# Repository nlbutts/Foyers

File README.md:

# Foyers / BackPorch Project

The Foyers/BackPorch system is an STM32-based hardware ecosystem designed for FRC robot sensing and control, featuring CAN communication with a built-in bootloader.

## Hardware Overview

### Foyer Distribution Board
The Foyer board serves as the primary distribution point for the system. 
- **Power & CAN Input**: Connects to the main robot power and CAN bus.
- **Power & CAN Exit**: Provides a pass-through for daisy-chaining CAN and power to subsequent devices.
- **Node Interface**: Distributes power and CAN to the BackPorch and sensor nodes.

### BackPorch Main Board
The BackPorch is the central controller board, based on the STM32G0B1 microcontroller. It handles high-level CAN communication, sensor aggregation, and basic power management.

#### Main Connectors & Pinouts

| Ref | Type | Function | Mating Part |
| --- | --- | --- | --- |
| **J4** | RJ45 | CAN Bus | Standard RJ45 Plug |
| **J9** | JST PH 6-pin | Rev Through Bore Encoder | JST PHR-6 |
| **J10** | USB Micro B | Power / Debug | Standard Micro-USB |
| **J1/J2**| Wago 2601 | Power Input (VBAT/GND) | 24-16 AWG Wire |
| **J3** | Wago 2601 | Motor Output | 24-16 AWG Wire |
| **J6** | Tag-Connect | SWD Programming | TC2030-IDC |

**J4 (RJ45) CAN Pinout:**
- **Pin 1**: CAN High
- **Pin 2**: CAN Low
- **Pin 3**: CAN High Loopback
- **Pin 4**: VBAT
- **Pin 5**: VBAT
- **Pin 6**: Can Low Loopback
- **Pin 7**: GND
- **Pin 8**: GND

**J9 (Rev Through Bore Encoder) Pinout:**
Compatible with the [REV Through Bore Encoder](https://docs.revrobotics.com/rev-crossover-products/sensors/tbe).
- **Pin 1**: 5V Power
- **Pin 2**: Absolute Position (Duty Cycle)
- **Pin 3**: Incremental Channel A
- **Pin 4**: Incremental Channel B
- **Pin 5**: Index (Optional)
- **Pin 6**: GND

### SimpleTOF Board
A compact Time-of-Flight (ToF) distance sensor breakout designed to interface with the BackPorch.

## Software Setup

### Development Environment
This project uses the official STM32 development workflow:

1.  **STM32CubeMX**: Used for low-level hardware configuration (GPIO, CAN, Timers).
    - Open the `.ioc` files in the `software/backporch` or `software/bootloader` directories to modify the hardware configuration.
    - Generate code to update the underlying HAL drivers.
2.  **Visual Studio Code**: The recommended IDE for code development.
    - Use the **STM32 VS Code Extension** to compile the project.
    - Ensure `arm-none-eabi-gcc` is installed and in your PATH.
    - Build using the `CMake` workflow provided by the extension.

## Bootloader & Monitoring Utility

The `software/can_mon/bp_debug.py` program is a multi-purpose Python utility for interacting with the hardware over CAN.

### Script Purpose
- **CAN Monitor**: Provides a real-time GUI to view telemetry from discovered devices (Voltage, Current, Temp, Distance, Encoder position).
- **Firmware Updater**: Acts as the host tool for the CAN bootloader, allowing you to stream `.bin` files to a target device ID and commit them to flash.
- **Status Broadcasts**: Decodes the WPILib-formatted CAN frames used by the system.

### Usage
```bash
python software/can_mon/bp_debug.py
```
*Note: Requires `python-can` and `tkinter` libraries. Ensure your CAN adapter is configured (default: SLSAN on COM5).*

## System Architecture

The system follows a modular architecture where multiple sensor nodes (Foyers) communicate with the BackPorch controller over a shared CAN bus, which then interfaces with the Robot Controller.

These are similar to the SWYFT CAN wiring devices

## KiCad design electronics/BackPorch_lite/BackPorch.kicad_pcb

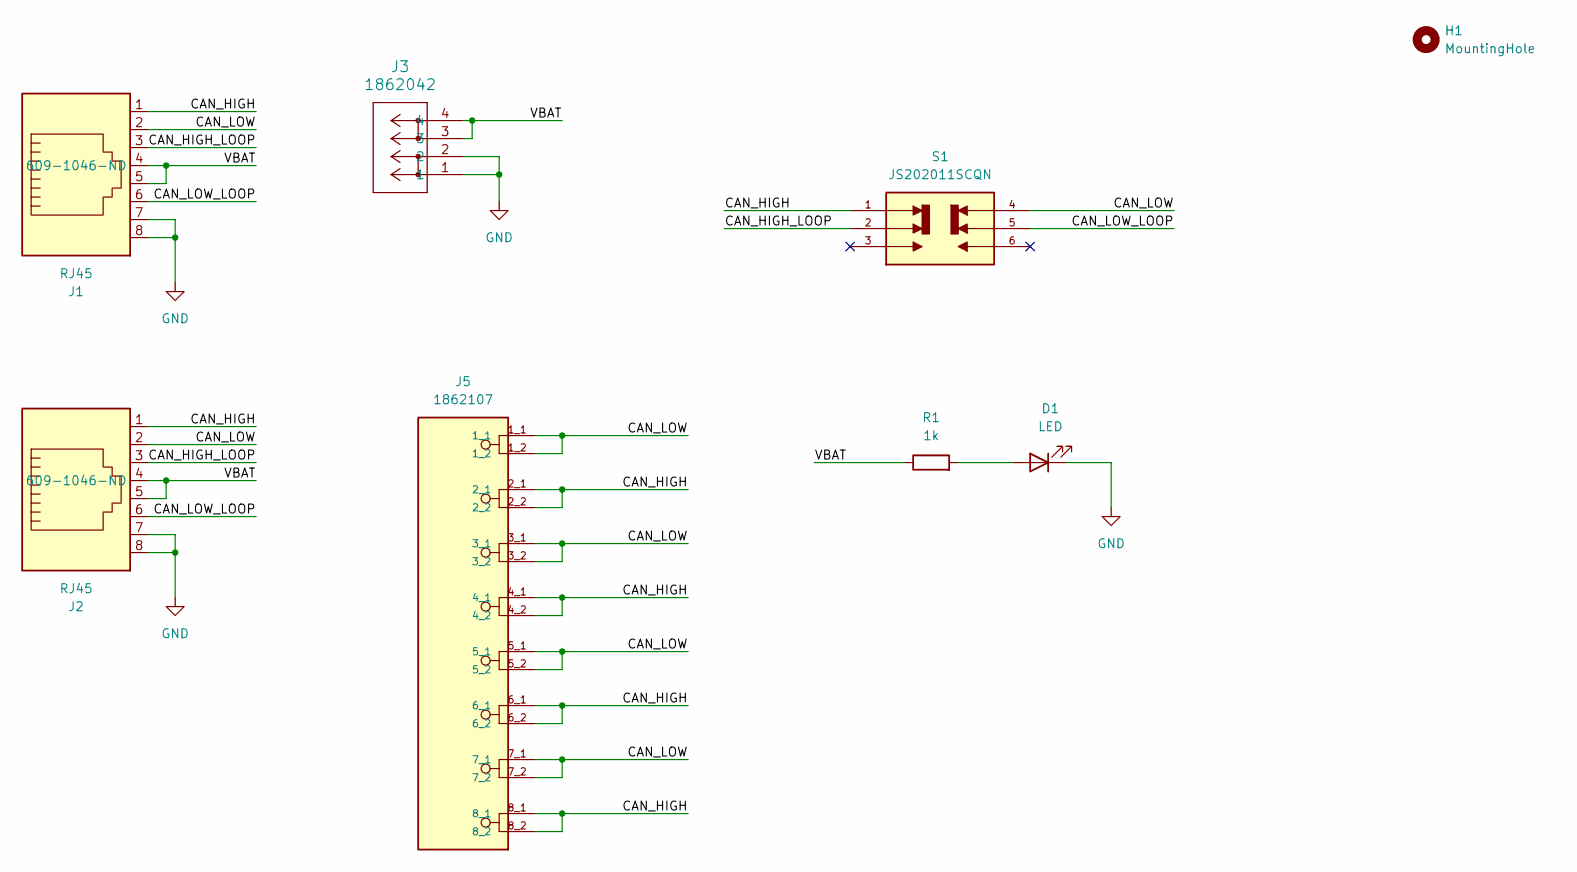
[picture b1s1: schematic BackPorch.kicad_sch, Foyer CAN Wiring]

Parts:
D1: LED; LED_0603_1608Metric_Pad1.05x0.95mm_HandSolder
H1: MountingHole; MountingHole_3.2mm_M3
J1, J2: RJ45; AMPHENOL_54602-908LF; Digikey 609-1046-ND
J3: 1862042; CONN_1862042
J5: 1862107; PHOENIX_1862107
R1: 1k; R_0603_1608Metric_Pad0.98x0.95mm_HandSolder
S1: JS202011SCQN; SW_JS202011SCQN; PARTREV 26 May 22

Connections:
/CAN_HIGH: J1.1, J2.1, J5.2_1, J5.2_2, J5.4_1, J5.4_2, J5.6_1, J5.6_2, J5.8_1, J5.8_2, S1.1
/CAN_HIGH_LOOP: J1.3, J2.3, S1.2
/CAN_LOW: J1.2, J2.2, J5.1_1, J5.1_2, J5.3_1, J5.3_2, J5.5_1, J5.5_2, J5.7_1, J5.7_2, S1.4
/CAN_LOW_LOOP: J1.6, J2.6, S1.5
/VBAT: J1.4, J1.5, J2.4, J2.5, J3.3, J3.4, R1.1
GND: D1.1 (K), J1.7, J1.8, J2.7, J2.8, J3.1, J3.2
unnamed: D1.2 (A), R1.2

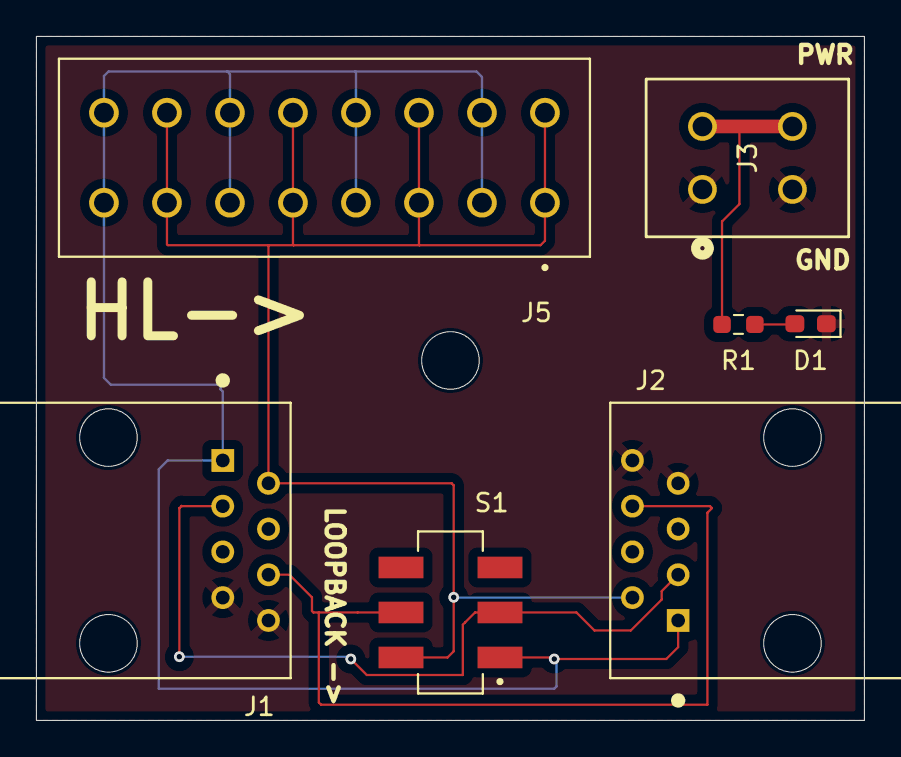
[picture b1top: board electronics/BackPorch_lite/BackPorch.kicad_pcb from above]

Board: 2 copper layers, 46.0 x 38.0 mm, 8 parts (0 on the bottom side), 7 nets.

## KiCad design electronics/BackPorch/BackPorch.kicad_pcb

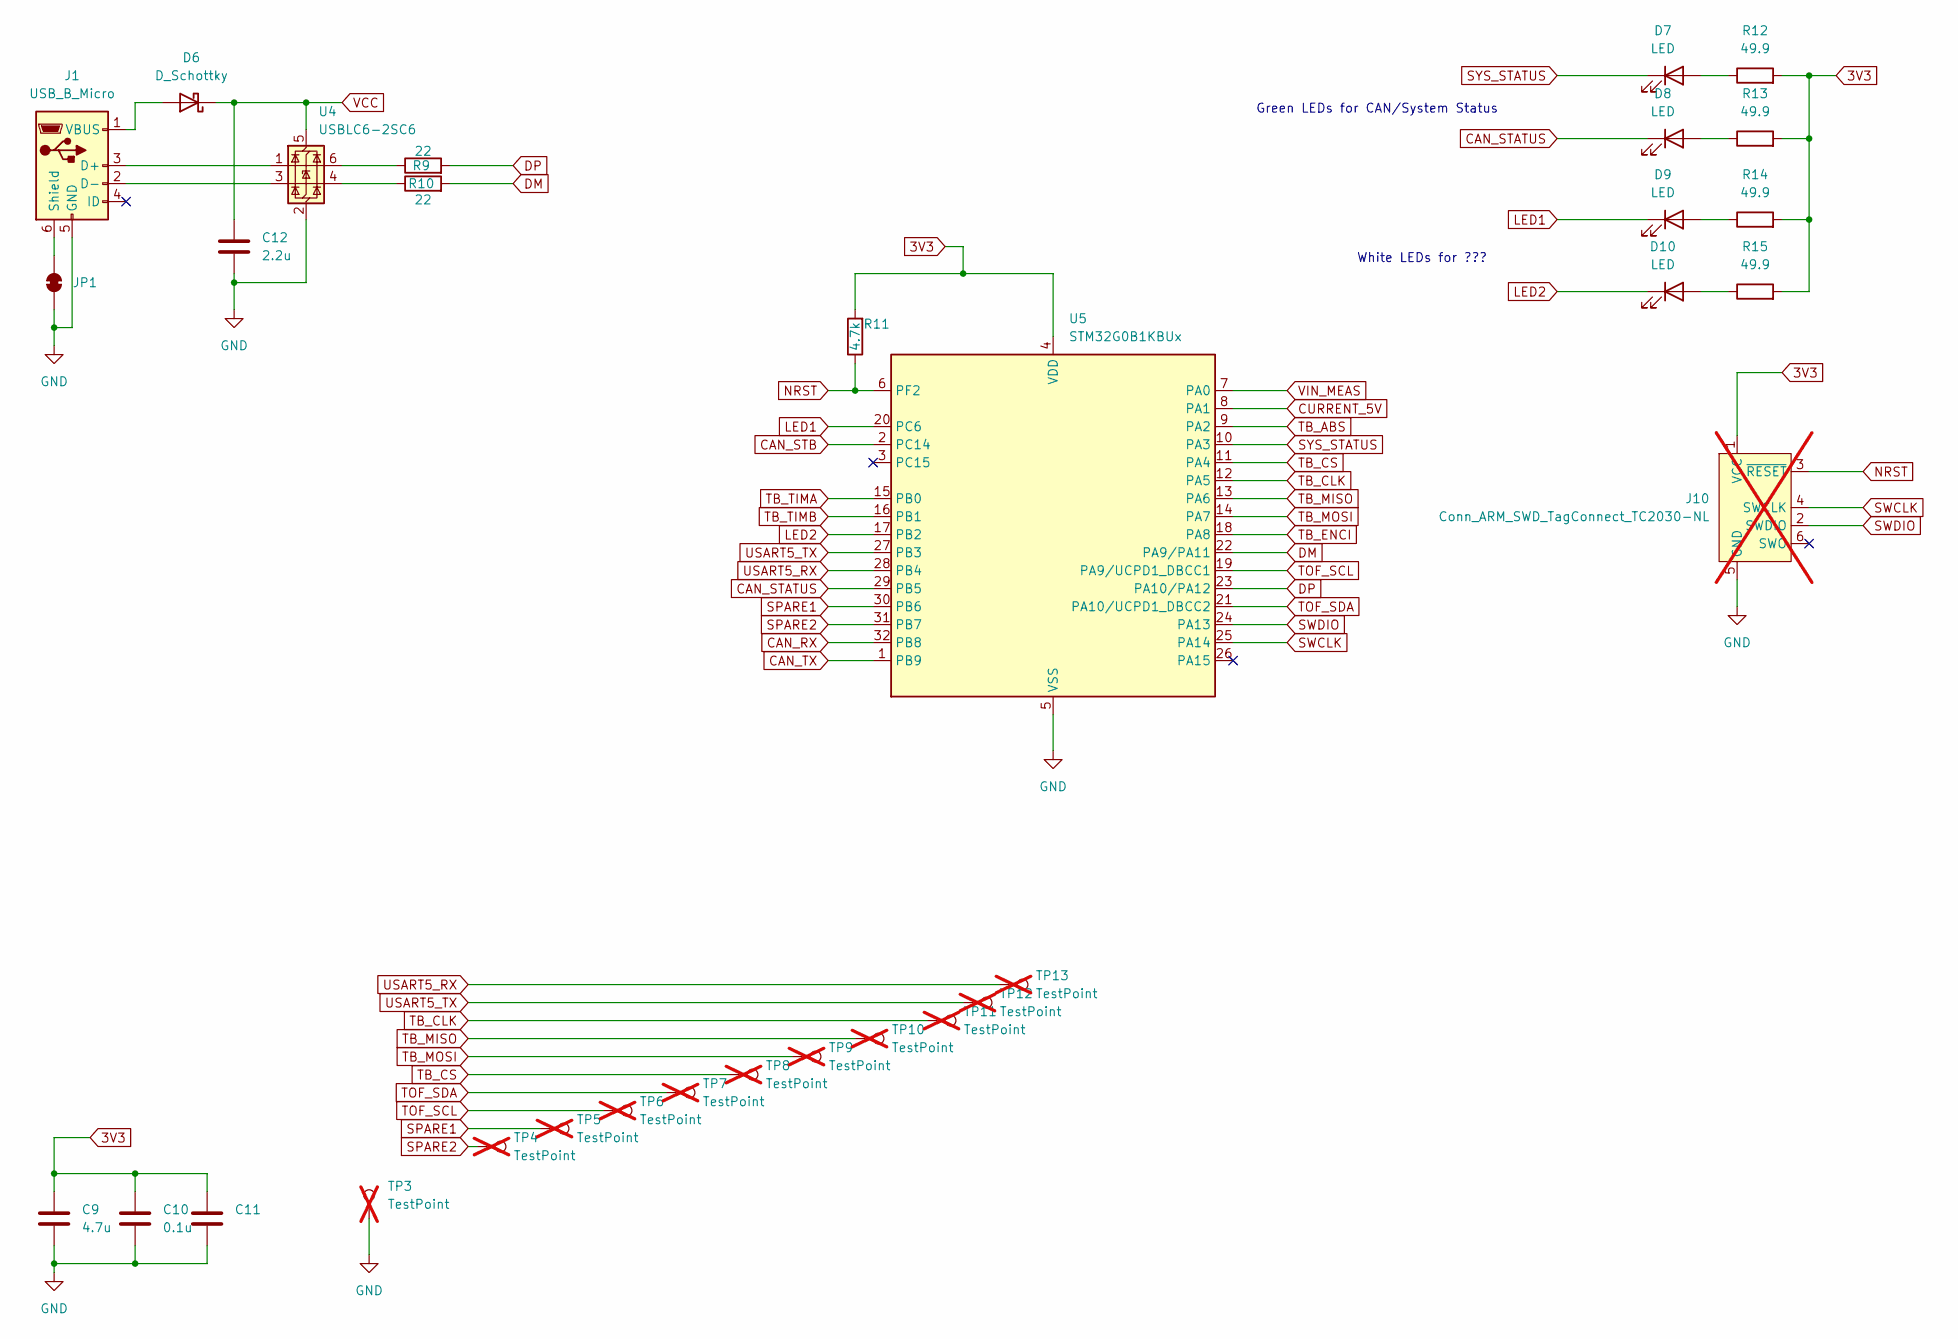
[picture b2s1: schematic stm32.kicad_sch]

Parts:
C9: 4.7u; C_0603_1608Metric; JLC C19666
C10, C11: 0.1u; C_0402_1005Metric; JLC C1525
C12: 2.2u; C_0603_1608Metric; JLC C23630
D6: D_Schottky; D_SOD-123; Digikey B0540W-FDICT-ND
D7, D8: LED; LED_0805_2012Metric; JLC C2297
D9, D10: LED; LED_0805_2012Metric; JLC C34499
J1: USB_B_Micro; USB_Micro-B_Amphenol_10118193-0001LF_Horizontal; JLC C132562
J10: Conn_ARM_SWD_TagConnect_TC2030-NL; Tag-Connect_TC2030-IDC-NL_2x03_P1.27mm_Vertical; not fitted
JP1: SolderJumper_2_Bridged; SolderJumper-2_P1.3mm_Bridged2Bar_RoundedPad1.0x1.5mm
R9, R10: 22; R_0402_1005Metric; JLC C25092
R11: 4.7k; R_0402_1005Metric; JLC C25900
R12, R13, R14, R15: 49.9; R_0402_1005Metric; JLC C25120
TP3, TP4, TP5, TP6, TP7, TP8, TP9, TP10, TP11, TP12, TP13: TestPoint; TestPoint_Pad_D1.0mm; not fitted
U4: USBLC6-2SC6; SOT-23-6; JLC C7519
U5: STM32G0B1KBUx; QFN-32-1EP_5x5mm_P0.5mm_EP3.45x3.45mm; JLC C5159549

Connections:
3V3: C9.1, C10.1, C11.1, J10.1 (VCC), R11.2, R12.2, R13.2, R14.2, R15.2, U5.4 (VDD); also elsewhere on the board
CAN_RX: U5.32 (PB8); also elsewhere on the board
CAN_STATUS: D8.1 (K), U5.29 (PB5)
CAN_STB: U5.2 (PC14); also elsewhere on the board
CAN_TX: U5.1 (PB9); also elsewhere on the board
CURRENT_5V: U5.8 (PA1); also elsewhere on the board
DM: R10.2, U5.22 (PA9/PA11)
DP: R9.2, U5.23 (PA10/PA12)
GND: C9.2, C10.2, C11.2, C12.1, J1.5 (GND), J10.5 (GND), JP1.1 (A), TP3.1, U4.2 (GND), U5.5 (VSS), U5.33 (VSS); also elsewhere on the board
LED1: D9.1 (K), U5.20 (PC6)
LED2: D10.1 (K), U5.17 (PB2)
NRST: J10.3 (~RESET), R11.1, U5.6 (PF2)
unnamed: D6.2 (A), J1.1 (VBUS)
unnamed: D7.2 (A), R12.1
unnamed: D8.2 (A), R13.1
unnamed: D9.2 (A), R14.1
unnamed: D10.2 (A), R15.1
unnamed: J1.6 (Shield), JP1.2 (B)
unnamed: R9.1, U4.6 (I/O1)
unnamed: R10.1, U4.4 (I/O2)
SPARE1: TP5.1, U5.30 (PB6)
SPARE2: TP4.1, U5.31 (PB7)
SWCLK: J10.4 (SWCLK), U5.25 (PA14)
SWDIO: J10.2 (SWDIO), U5.24 (PA13)
SYS_STATUS: D7.1 (K), U5.10 (PA3)
TB_ABS: U5.9 (PA2); also elsewhere on the board
TB_CLK: TP11.1, U5.12 (PA5); also elsewhere on the board
TB_CS: TP8.1, U5.11 (PA4); also elsewhere on the board
TB_ENCI: U5.18 (PA8); also elsewhere on the board
TB_MISO: TP10.1, U5.13 (PA6); also elsewhere on the board
TB_MOSI: TP9.1, U5.14 (PA7); also elsewhere on the board
TB_TIMA: U5.15 (PB0); also elsewhere on the board
TB_TIMB: U5.16 (PB1); also elsewhere on the board
TOF_SCL: TP6.1, U5.19 (PA9/UCPD1_DBCC1); also elsewhere on the board
TOF_SDA: TP7.1, U5.21 (PA10/UCPD1_DBCC2); also elsewhere on the board
USART5_RX: TP13.1, U5.28 (PB4)
USART5_TX: TP12.1, U5.27 (PB3)
VCC: C12.2, D6.1 (K), U4.5 (VBUS); also elsewhere on the board
VIN_MEAS: U5.7 (PA0); also elsewhere on the board

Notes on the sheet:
Green LEDs for CAN/System Status
White LEDs for ???

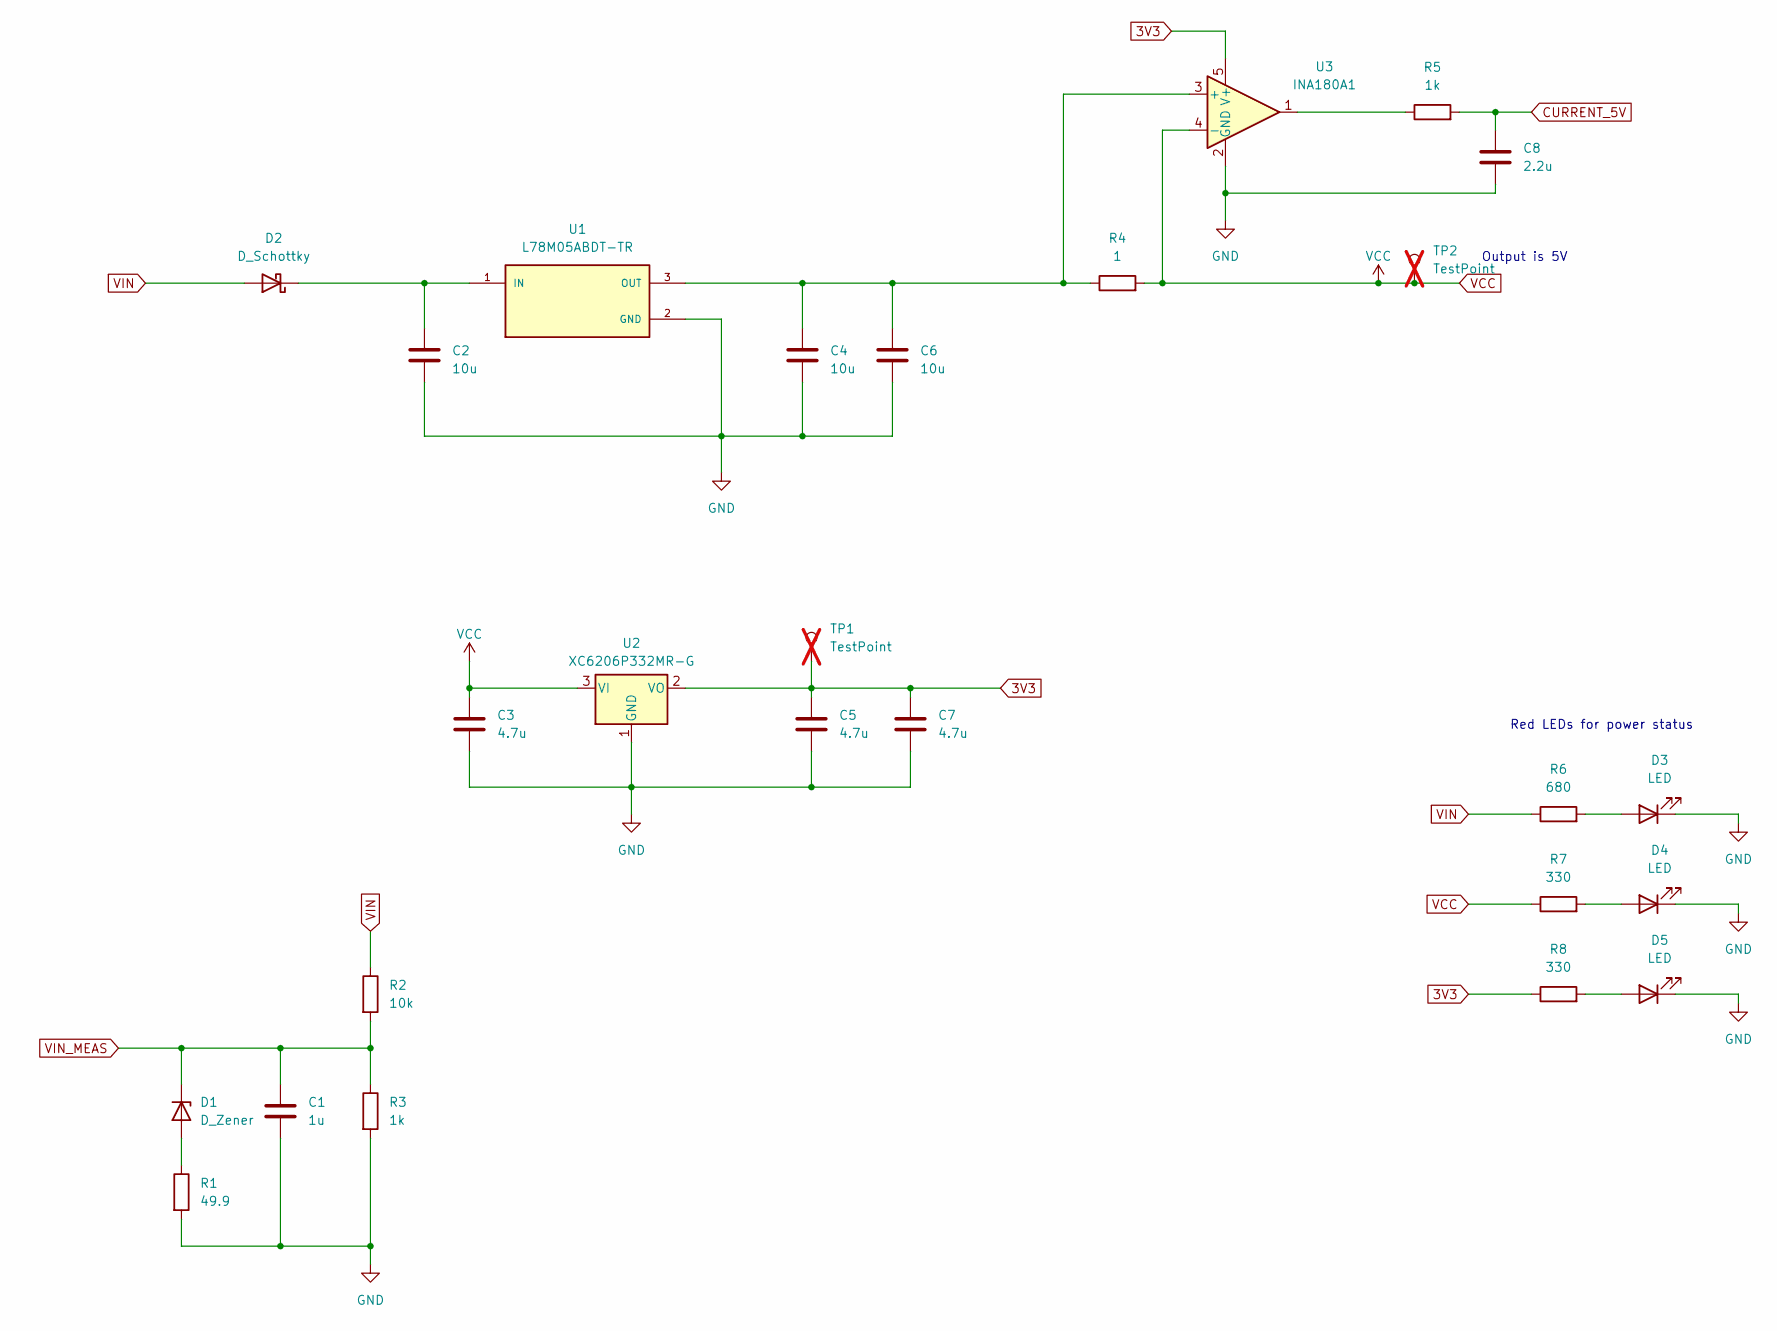
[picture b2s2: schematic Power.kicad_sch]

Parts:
C1: 1u; C_0402_1005Metric; JLC C52923
C2, C4, C6: 10u; C_0603_1608Metric; Digikey 490-5523-1-ND
C3, C5, C7: 4.7u; C_0603_1608Metric; JLC C19666
C8: 2.2u; C_0603_1608Metric; JLC C23630
D1: D_Zener; D_SOD-123; JLC C2105
D2: D_Schottky; D_SOD-123; Digikey B0540W-FDICT-ND
D3, D4, D5: LED; LED_0603_1608Metric; JLC C2286
R1: 49.9; R_0805_2012Metric; JLC C17720
R2: 10k; R_0402_1005Metric; JLC C25744
R3, R5: 1k; R_0402_1005Metric; JLC C11702
R4: 1; R_0603_1608Metric; JLC C22936
R6: 680; R_0603_1608Metric; JLC C23228
R7, R8: 330; R_0603_1608Metric; JLC C23138
TP1, TP2: TestPoint; TestPoint_Pad_D1.0mm; not fitted
U1: L78M05ABDT-TR; TO-252-2; PARTREV 23; JLC C58069
U2: XC6206P332MR-G; SOT-23; JLC C5446
U3: INA180A1; SOT-23-5; JLC C122228

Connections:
3V3: C5.1, C7.1, R8.1, TP1.1, U2.2 (VO), U3.5 (V+); also elsewhere on the board
CURRENT_5V: C8.2, R5.2; also elsewhere on the board
GND: C1.2, C2.2, C3.2, C4.2, C5.2, C6.2, C7.2, C8.1, D3.1 (K), D4.1 (K), D5.1 (K), R1.2, R3.2, U1.2 (GND), U2.1 (GND), U3.2 (GND); also elsewhere on the board
unnamed: D1.2 (A), R1.1
unnamed: C2.1, D2.1 (K), U1.1 (IN)
unnamed: D3.2 (A), R6.2
unnamed: D4.2 (A), R7.2
unnamed: D5.2 (A), R8.2
unnamed: R5.1, U3.1
unnamed: C4.1, C6.1, R4.1, U1.3 (OUT), U3.3 (+)
VCC: C3.1, R4.2, R7.1, TP2.1, U2.3 (VI), U3.4 (-); also elsewhere on the board
VIN: D2.2 (A), R2.1, R6.1; also elsewhere on the board
VIN_MEAS: C1.1, D1.1 (K), R2.2, R3.1; also elsewhere on the board

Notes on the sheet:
Output is 5V
Red LEDs for power status

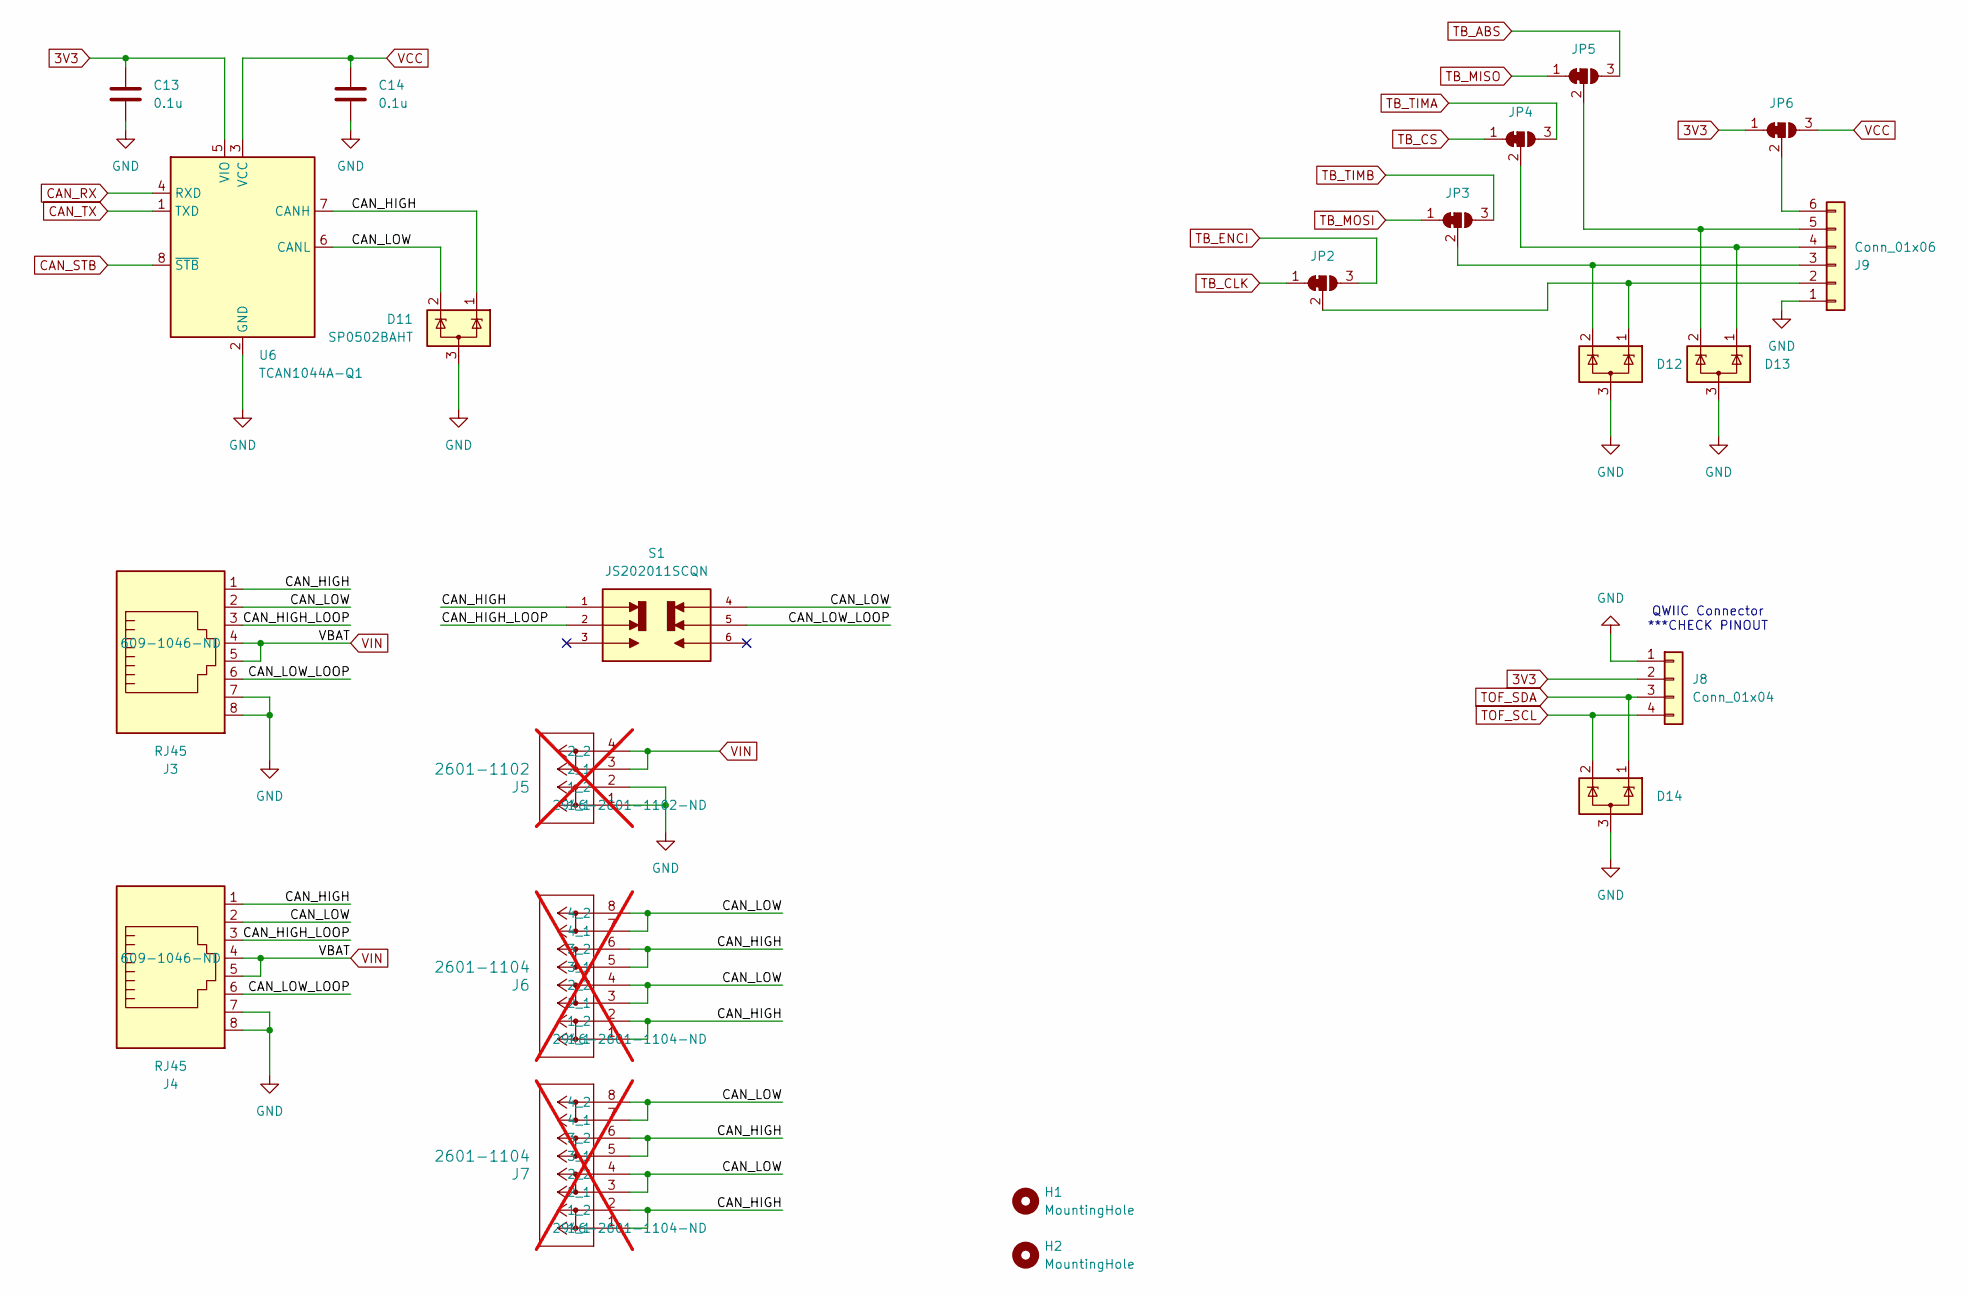
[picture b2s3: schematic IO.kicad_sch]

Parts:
C13, C14: 0.1u; C_0402_1005Metric; JLC C1525
D11, D12, D13, D14: SP0502BAHT; SOT-23; JLC C32677
H1, H2: MountingHole; MountingHole_3.2mm_M3_DIN965
J3, J4: RJ45; AMPHENOL_54602-908LF; Digikey 609-1046-ND
J5: 2601-1102; CONN2_2601-1102_WAG; Digikey 2946-2601-1102-ND; not fitted
J6, J7: 2601-1104; CONN4_2601-1104_WAG; Digikey 2946-2601-1104-ND; not fitted
J8: Conn_01x04; JST_SH_SM04B-SRSS-TB_1x04-1MP_P1.00mm_Horizontal; Digikey 455-B4B-PH-SM4-TBCT-ND
J9: Conn_01x06; JST_PH_S6B-PH-K_1x06_P2.00mm_Horizontal; JLC C157920
JP2, JP3, JP4, JP5: SolderJumper_3_Bridged12; SolderJumper-3_P1.3mm_Bridged12_RoundedPad1.0x1.5mm
JP6: SolderJumper_3_Bridged12; SolderJumper-3_P1.3mm_Bridged2Bar12_RoundedPad1.0x1.5mm_Num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
S1: JS202011SCQN; SW_JS202011SCQN; PARTREV 26 May 22; JLC C221666
U6: TCAN1044A-Q1; VSON-8-1EP_3x3mm_P0.65mm_EP1.6x2.4mm; JLC C3234119

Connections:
3V3: C13.1, J8.2, JP6.1 (A), U6.5 (VIO); also elsewhere on the board
/IO/CAN_HIGH: D11.1 (K), J3.1, J4.1, J6.1 (1_1), J6.2 (1_2), J6.5 (3_1), J6.6 (3_2), J7.1 (1_1), J7.2 (1_2), J7.5 (3_1), J7.6 (3_2), S1.1, U6.7 (CANH)
/IO/CAN_HIGH_LOOP: J3.3, J4.3, S1.2
/IO/CAN_LOW: D11.2 (K), J3.2, J4.2, J6.3 (2_1), J6.4 (2_2), J6.7 (4_1), J6.8 (4_2), J7.3 (2_1), J7.4 (2_2), J7.7 (4_1), J7.8 (4_2), S1.4, U6.6 (CANL)
/IO/CAN_LOW_LOOP: J3.6, J4.6, S1.5
CAN_RX: U6.4 (RXD); also elsewhere on the board
CAN_STB: U6.8 (~STB); also elsewhere on the board
CAN_TX: U6.1 (TXD); also elsewhere on the board
GND: C13.2, C14.2, D11.3 (A), D12.3 (A), D13.3 (A), D14.3 (A), J3.7, J3.8, J4.7, J4.8, J5.1 (1_1), J5.2 (1_2), J8.1, J9.1, U6.2 (GND); also elsewhere on the board
unnamed: D12.1 (K), J9.2, JP2.2 (C)
unnamed: D12.2 (K), J9.3, JP3.2 (C)
unnamed: D13.1 (K), J9.4, JP4.2 (C)
unnamed: D13.2 (K), J9.5, JP5.2 (C)
unnamed: J9.6, JP6.2 (C)
TB_ABS: JP5.3 (B); also elsewhere on the board
TB_CLK: JP2.1 (A); also elsewhere on the board
TB_CS: JP4.1 (A); also elsewhere on the board
TB_ENCI: JP2.3 (B); also elsewhere on the board
TB_MISO: JP5.1 (A); also elsewhere on the board
TB_MOSI: JP3.1 (A); also elsewhere on the board
TB_TIMA: JP4.3 (B); also elsewhere on the board
TB_TIMB: JP3.3 (B); also elsewhere on the board
TOF_SCL: D14.2 (K), J8.4; also elsewhere on the board
TOF_SDA: D14.1 (K), J8.3; also elsewhere on the board
VCC: C14.1, JP6.3 (B), U6.3 (VCC); also elsewhere on the board
VIN: J3.4, J3.5, J4.4, J4.5, J5.3 (2_1), J5.4 (2_2); also elsewhere on the board

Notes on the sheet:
QWIIC Connector ***CHECK PINOUT

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
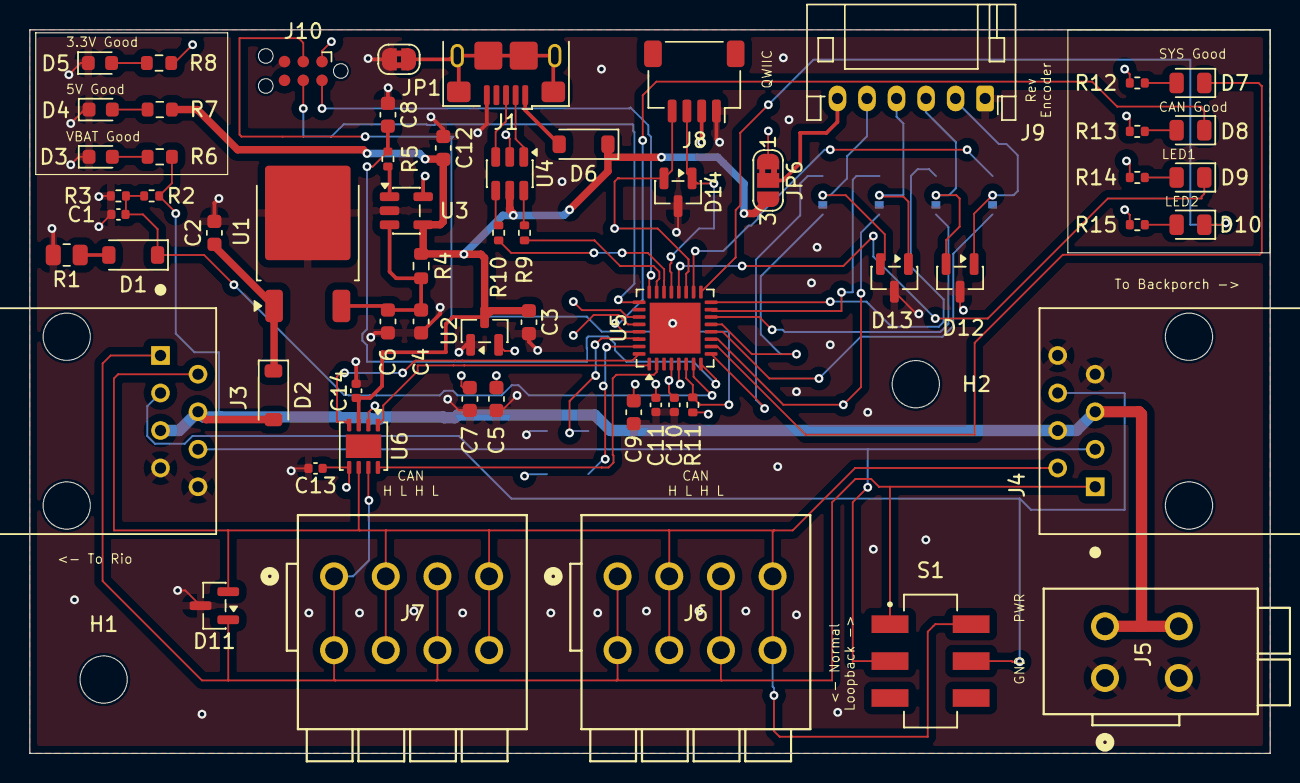
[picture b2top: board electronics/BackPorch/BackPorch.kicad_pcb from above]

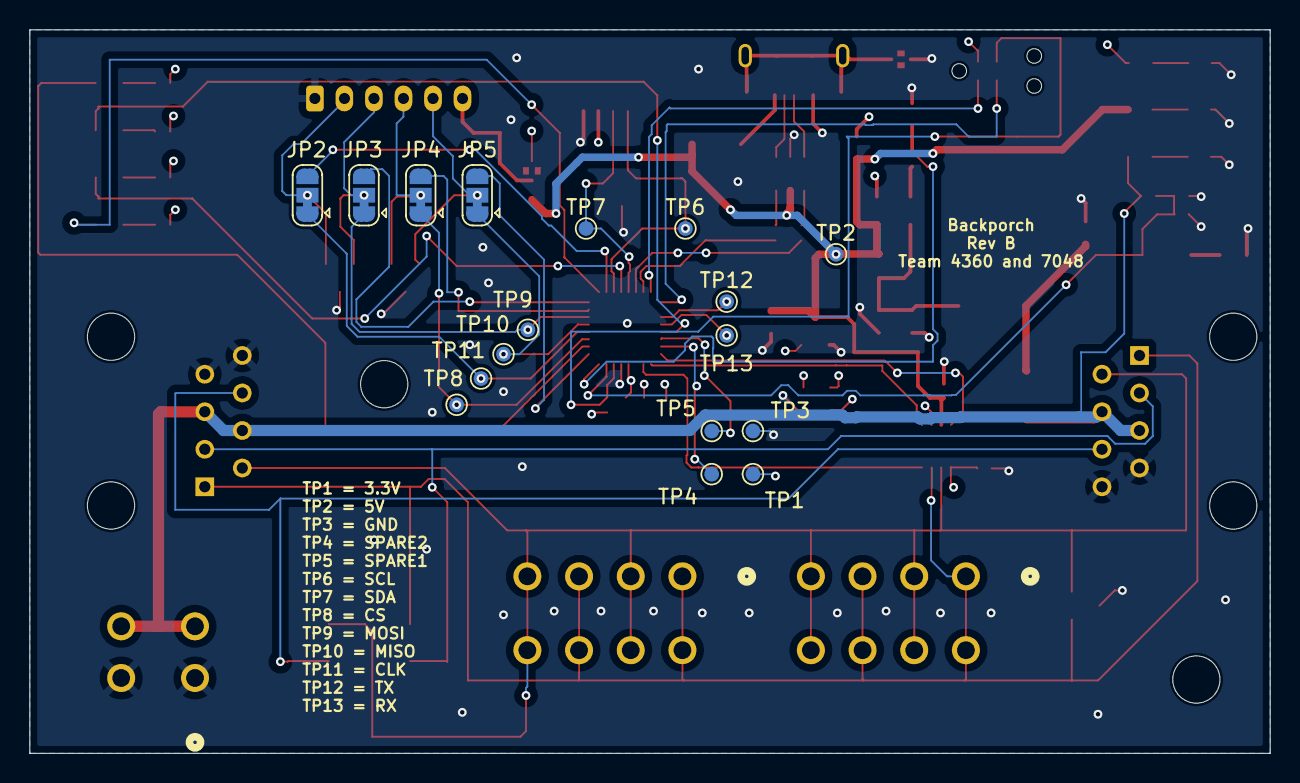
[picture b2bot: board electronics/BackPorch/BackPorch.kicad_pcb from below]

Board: 4 copper layers, 84.0 x 49.0 mm, 80 parts (17 on the bottom side), 58 nets.

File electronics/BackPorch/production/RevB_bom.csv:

Designator,Footprint,Quantity,Value,LCSC Part #
C1,0402,1,1u,C52923
"C10, C11, C13, C14",0402,4,0.1u,C1525
"C12, C8",0603,2,2.2u,C23630
"C2, C4, C6",0603,3,10u,C96446
"C3, C5, C7, C9",0603,4,4.7u,C19666
D1,D_SOD-123,1,D_Zener,C2105
"D10, D9",0805,2,LED,C34499
"D11, D12, D13, D14",SOT-23,4,SP0502BAHT,C32677
"D2, D6",D_SOD-123,2,D_Schottky,C8598
"D3, D4, D5",0603,3,LED,C2286
"D7, D8",0805,2,LED,C2297
J1,USB_Micro-B_Amphenol_10118193-0001LF_Horizontal,1,USB_B_Micro,C132562
"J3, J4",AMPHENOL_54602-908LF,2,RJ45,C2847314
J8,JST_SH_SM04B-SRSS-TB_1x04-1MP_P1.00mm_Horizontal,1,Conn_01x04,C160404
J9,JST_PH_S6B-PH-K_1x06_P2.00mm_Horizontal,1,Conn_01x06,C157920
R1,0805,1,49.9,C17720
"R10, R9",0402,2,22,C25092
R11,0402,1,4.7k,C25900
"R12, R13, R14, R15",0402,4,49.9,C25120
R2,0402,1,10k,C25744
"R3, R5",0402,2,1k,C11702
R4,0603,1,1,C22936
R6,0603,1,680,C23228
"R7, R8",0603,2,330,C23138
S1,SW_JS202011SCQN,1,JS202011SCQN,C221666
U1,TO-252-2,1,L78M05ABDT-TR,C58069
U2,SOT-23,1,XC6206P332MR-G,C5446
U3,SOT-23-5,1,INA180A1,C122228
U4,SOT-23-6,1,USBLC6-2SC6,C7519
U5,QFN-32-1EP_5x5mm_P0.5mm_EP3.45x3.45mm,1,STM32G0B1KBUx,C5159549
U6,VSON-8-1EP_3x3mm_P0.65mm_EP1.6x2.4mm,1,TCAN1044A-Q1,C3234119

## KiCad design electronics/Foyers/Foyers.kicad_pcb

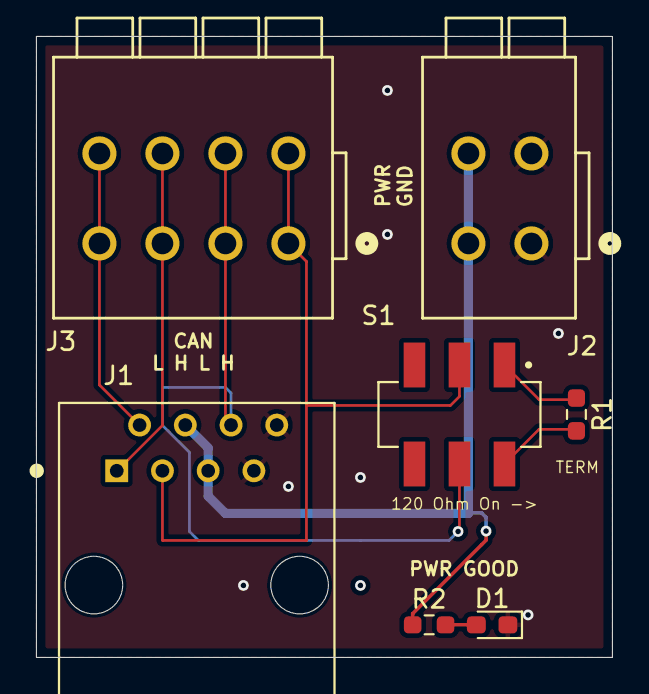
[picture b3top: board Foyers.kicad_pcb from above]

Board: 2 copper layers, 32.0 x 34.5 mm, 7 parts (0 on the bottom side), 9 nets.

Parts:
D1: LED; LED_0603_1608Metric_Pad1.05x0.95mm_HandSolder
J1: RJ45; AMPHENOL_54602-908LF
J2: 2601-1102; CONN2_2601-1102_WAG
J3: 2601-1104; CONN4_2601-1104_WAG
R1: 120; R_0603_1608Metric_Pad0.98x0.95mm_HandSolder
R2: 680; R_0603_1608Metric_Pad0.98x0.95mm_HandSolder
S1: JS202011SCQN; SW_JS202011SCQN

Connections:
/CAN_HIGH: J1.1, J3.5 (3_1), J3.6 (3_2)
/CAN_HIGH_LOOP: J1.3, J3.1 (1_1), J3.2 (1_2), S1.2
/CAN_LOW: J1.2, J3.7 (4_1), J3.8 (4_2)
/CAN_LOW_LOOP: J1.6, J3.3 (2_1), J3.4 (2_2), S1.5
/VBAT: J1.4, J1.5, J2.3 (2_1), J2.4 (2_2), R2.1
GND: D1.1 (K), J1.7, J1.8, J2.1 (1_1), J2.2 (1_2)
unnamed: D1.2 (A), R2.2
unnamed: R1.1, S1.1
unnamed: R1.2, S1.4

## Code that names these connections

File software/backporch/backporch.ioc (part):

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Mcu.Name=STM32G0B1K(B-C-E)Ux
Mcu.Package=UFQFPN32
Mcu.UserName=STM32G0B1KBUx
PA0.GPIOParameters=GPIO_Label
PA0.GPIO_Label=VIN_MEASURE
PA0.Mode=IN0
PA0.Signal=ADC1_IN0
PA1.GPIOParameters=GPIO_Label
PA1.GPIO_Label=CURRENT_5V
PA1.Mode=IN1
PA1.Signal=ADC1_IN1
PA10.Mode=I2C
PA10.Signal=I2C1_SDA
PA11\ [PA9].Mode=Device
PA11\ [PA9].Signal=USB_DM
PA12\ [PA10].Mode=Device
PA12\ [PA10].Signal=USB_DP
PA13.Mode=Serial_Wire
PA13.Signal=SYS_SWDIO
PA14-BOOT0.Mode=Serial_Wire
PA14-BOOT0.Signal=SYS_SWCLK
PA2.Signal=S_TIM2_CH3
PA3.GPIOParameters=GPIO_Label
PA3.GPIO_Label=SYS_STATUS
PA3.Signal=GPIO_Output
PA8.GPIOParameters=GPIO_Label
PA8.GPIO_Label=TB_ENCI
PA8.Signal=S_TIM1_CH1
PA9.Mode=I2C
PA9.Signal=I2C1_SCL
PB0.GPIOParameters=GPIO_Label
PB0.GPIO_Label=TB_TIMA
PB0.Signal=S_TIM3_CH3
PB1.GPIOParameters=GPIO_Label
PB1.GPIO_Label=TB_TIMB
PB1.Signal=S_TIM3_CH4
PB2.GPIOParameters=GPIO_Label
PB2.GPIO_Label=LED2
PB2.Signal=GPIO_Output
PB3.Mode=Asynchronous
PB3.Signal=USART5_TX
PB4.Mode=Asynchronous
PB4.Signal=USART5_RX
PB5.GPIOParameters=GPIO_Label
PB5.GPIO_Label=CAN_STATUS
PB5.Signal=GPIO_Output
PB6.GPIOParameters=GPIO_Label
PB6.GPIO_Label=SPARE1
PB6.Signal=GPIO_Output
PB7.GPIOParameters=GPIO_Label
PB7.GPIO_Label=SPARE2
PB7.Signal=GPIO_Output
PB8.Mode=FDCAN_Activate
PB8.Signal=FDCAN1_RX
PB9.Mode=FDCAN_Activate
PB9.Signal=FDCAN1_TX
PC14-OSC32_IN\ (PC14).GPIOParameters=GPIO_Label
PC14-OSC32_IN\ (PC14).GPIO_Label=CAN_STB
PC14-OSC32_IN\ (PC14).Signal=GPIO_Output
PC6.GPIOParameters=GPIO_Label
PC6.GPIO_Label=LED1
PC6.Signal=GPIO_Output
RCC.HSE_VALUE=16000000
RCC.SYSCLKFreq_VALUE=64000000
RCC.SYSCLKSource=RCC_SYSCLKSOURCE_PLLCLK
board=custom

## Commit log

2025-06-20 Actually checked in the files.
2025-12-30 Planning on ordering more back porches.
2026-01-18 Various updates to the footprints. Added datasheets.
2026-01-18 Added the software.
2026-01-18 Verified CAN, voltage input, current reading although the resistor is off, and temperature reading.
2026-01-18 Many updates to get things dialed in. Have the ABS signal working. But there is a small glitch to it.
2026-01-19 Inc encoder is now working as well.
2026-01-19 Added a bootloader.
2026-01-19 Bootloader is working to the point it can push new images into app code space.
2026-01-19 Refactored the CAN messages. Programming is working, at least pushing code. Build version strings are working correctly.
2026-01-19 Bootblock will reboot on watchdog and stay in the bootblock.
2026-01-19 Forgot to add the auto increment version.
2026-01-20 Updated the bootblock functionality. I am able to program an app code image now.
2026-01-20 I can now reprogram app code from app code.
2026-01-20 Bootloading is working well.
2026-01-20 Updated the README file. It still needs some work.
2026-01-26 The bootblock now allows me to reprogram the bootblock.
2026-01-26 Many refactors to support different deviceIDs. Currently app code can't write to FLASH.
2026-02-07 This is mostly working.
2026-02-07 Things are working well. I can reprogram different units. The CAN status LED flashes as heartbeat messages come in.
2026-02-07 In the app added CAN bus utilization, sorted by device ID. Changed to the release build for the backporch, changed task names, moved can TX tasks into one thread and CAN Rx tasks into a second thread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
2026-02-07 Added the wpilib code. I have only tested the Java code and it works.
2026-02-10 Pulling Rev B into main (#1)
    * Planning on ordering more back porches.
    * Various updates to the footprints. Added datasheets.
    * Added the software.
    * Verified CAN, voltage input, current reading although the resistor is off, and temperature reading.
    * Many updates to get things dialed in. Have the ABS signal working. But there is a small glitch to it.
    * Inc encoder is now working as well.
2026-02-16 Rev b (#2)
    * Planning on ordering more back porches.
    * Various updates to the footprints. Added datasheets.
    * Added the software.
    * Verified CAN, voltage input, current reading although the resistor is off, and temperature reading.
    * Many updates to get things dialed in. Have the ABS signal working. But there is a small glitch to it.
    * Inc encoder is now working as well.
2026-02-22 Added the back porch lite devices.
2026-02-22 Added the backporch lite devices.
2026-02-22 Added a limit switch feature. TODO: Add the ability to switch between I2C/TOF mode and GPIO Limit switch mode.
2026-02-22 Minor changes to fix the CPU Usage stats.
2026-02-23 Added in the VL53L0C sensor library.
2026-02-24 Added in the TOF sensor.
2026-02-28 Added the TOF vs limit switch logic.
2026-03-20 Added a 3mf file for the backporch top.
2026-03-20 Added a backporch server and will update the app to connect to it.
2026-03-20 I have the backporch_server working. It doesn't work to program code yet.
2026-03-20 Slowed down the app's CAN transmit rate to get programming to work. It is no ideal.

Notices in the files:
electronics/BackPorch/BackPorch.kicad_sch:
Copyright 2025 Nick Butts
